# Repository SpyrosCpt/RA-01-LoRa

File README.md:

# RA-01-LoRa Dev Board

## Features
- Max 15V DC input
- 5V DC USB input
- CP2102 USB interface
- STM32F030RCT6
- 0.96" 128 x 32 OLED
- RA-01 LoRA Module
- LM35 Temperature Sensor
- AT93C46 EEPROM
- 4 Way DIP Switch
- 4 Push Buttons
- STM32 programming by SWD

## Firmware Example Provided
- Press Push Button 1 to Send LoRA Packet, you can change the data to send by editing TestLoraTransmit("packet to send")
- When not transmitting LoRA radio is in Receiver mode and will display any messages receievd
- Temperature Monitoring of LM35 will be displayed on OLED

## Hardware Version 1.1

## Firmware Change Log
- Changed frequency down from 915Mhz to 433MHz
- Oled working
- LoRa working
- EEPROM working
- Temp Sensor

## Harware Change Log
- Removed USB protection IC
- Swapped TX and RX lines
- Grounded pin 16 + 17 on OLED connector
- Moved LM34 Vcc from 3.3V to 5V

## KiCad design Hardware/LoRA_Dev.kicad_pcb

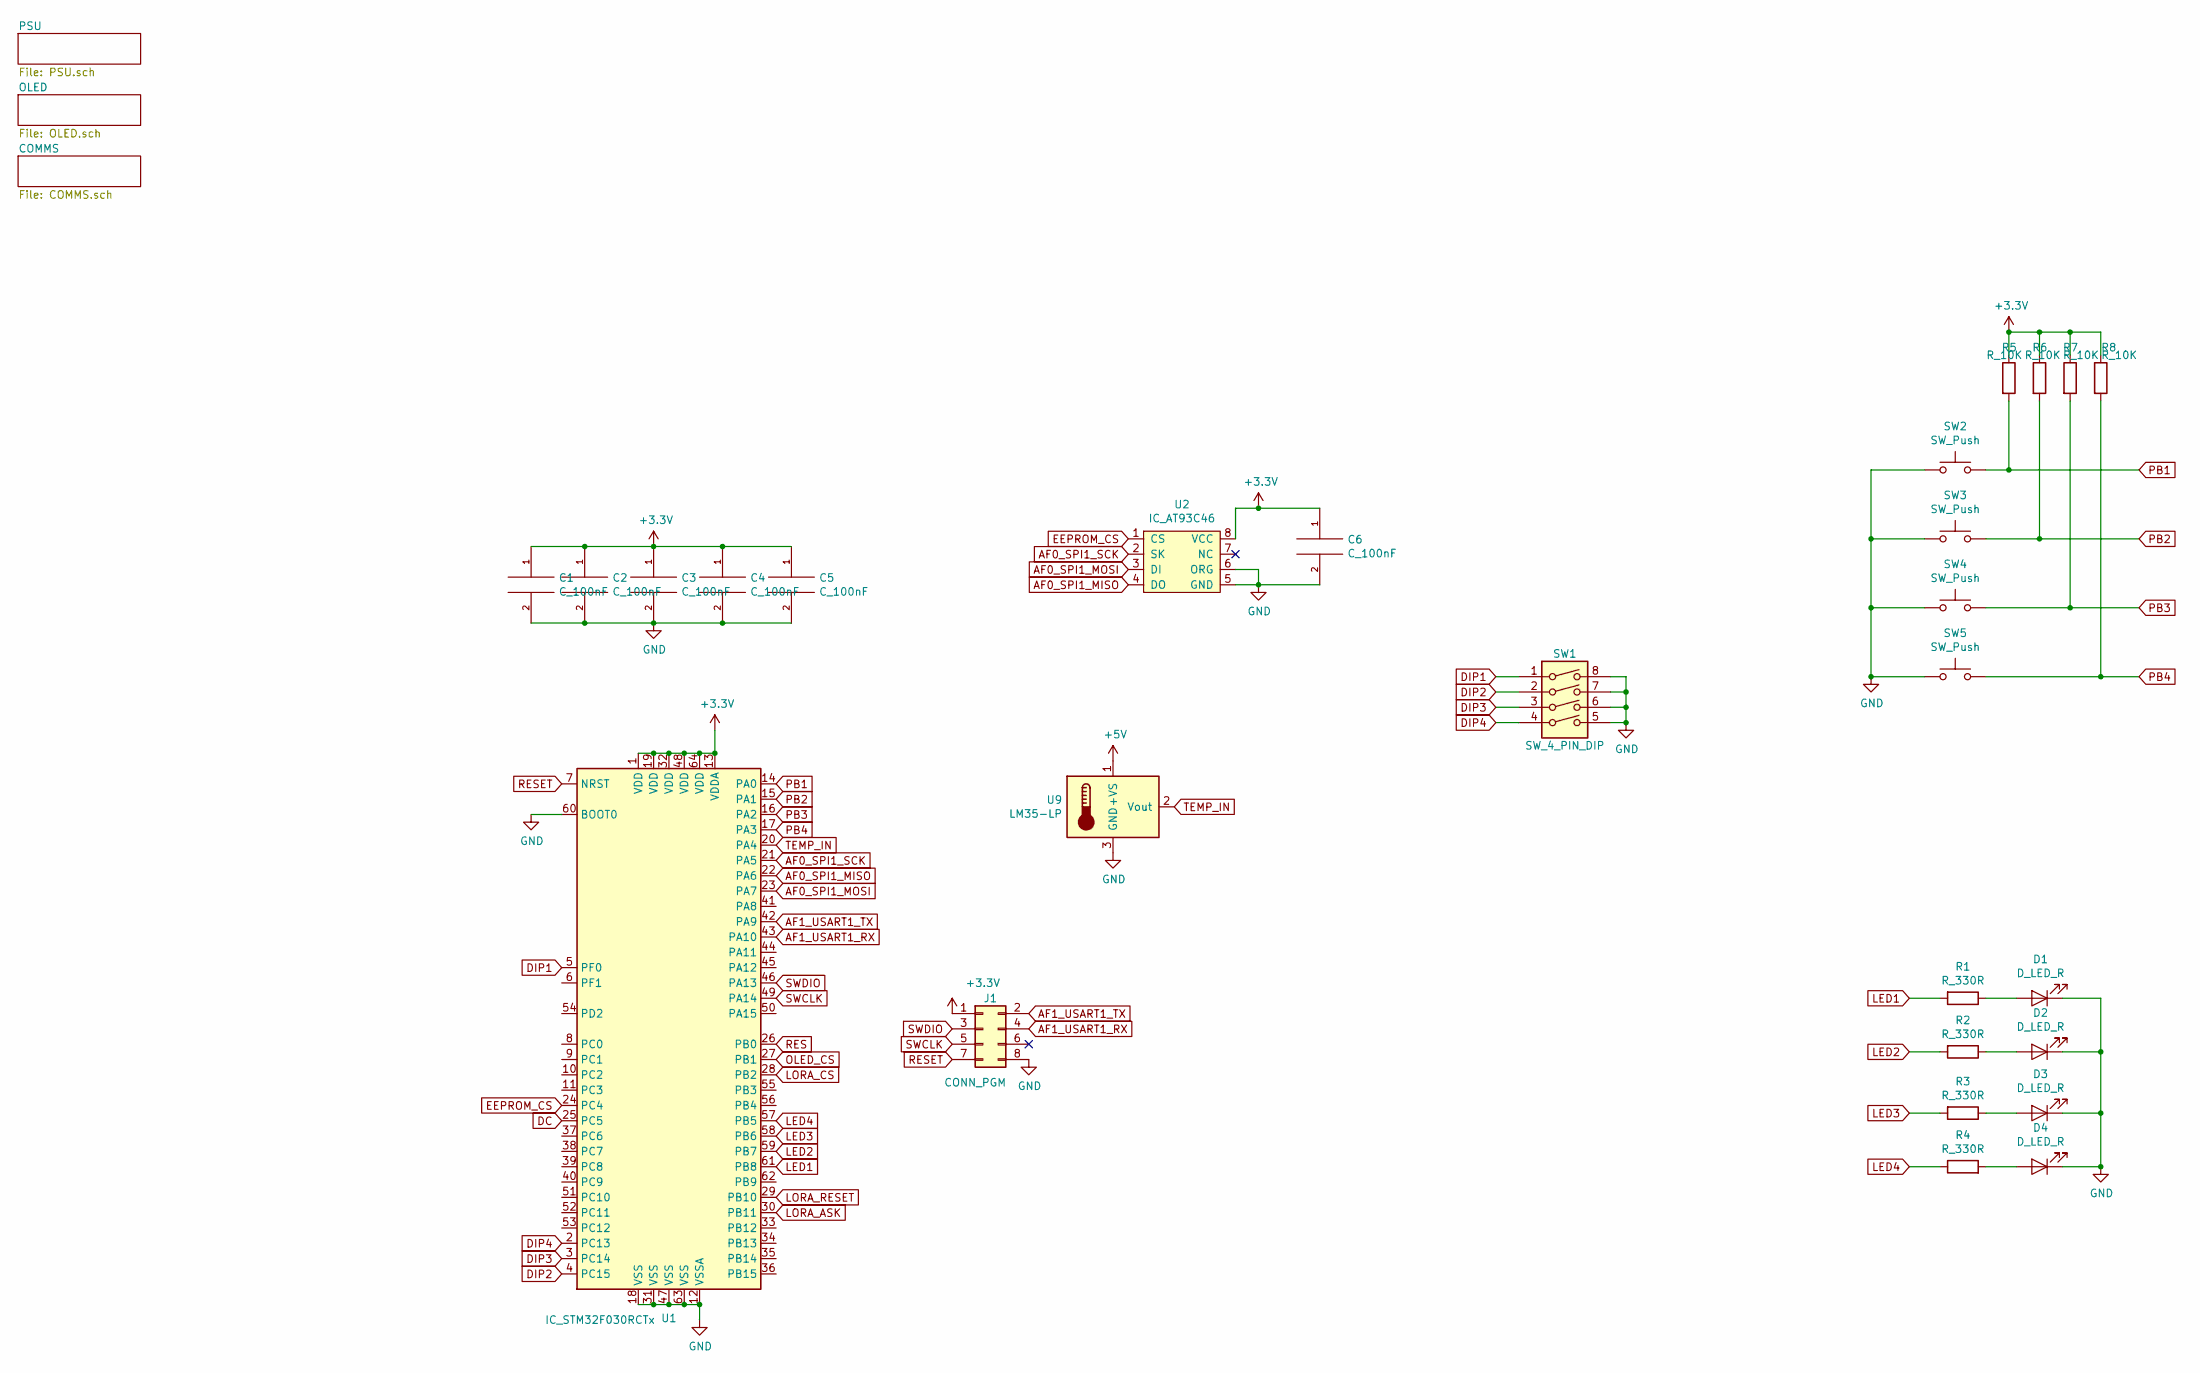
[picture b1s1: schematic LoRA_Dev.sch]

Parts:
C1, C2, C3, C4, C5, C6: C_100nF; C_0603_1608Metric_Pad1.05x0.95mm_HandSolder
D1, D2, D3, D4: D_LED_R; LED_0805_2012Metric_Pad1.15x1.40mm_HandSolder
J1: CONN_PGM; PinHeader_2x04_P2.54mm_Vertical
R1, R2, R3, R4: R_330R; R_0603_1608Metric_Pad1.05x0.95mm_HandSolder
R5, R6, R7, R8: R_10K; R_0603_1608Metric_Pad1.05x0.95mm_HandSolder
SW1: SW_4_PIN_DIP; SW_DIP_SPSTx04_Slide_9.78x12.34mm_W7.62mm_P2.54mm
SW2, SW3, SW4, SW5: SW_Push; SW_SPST_PTS645
U1: IC_STM32F030RCTx; LQFP-64_10x10mm_P0.5mm
U2: IC_AT93C46; SOIC-8_3.9x4.9mm_P1.27mm
U9: LM35-LP; TO-92

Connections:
+3V3: C1.1, C2.1, C3.1, C4.1, C5.1, C6.1, J1.1, R5.1, R6.1, R7.1, R8.1, U1.1 (VDD), U1.13 (VDDA), U1.19 (VDD), U1.32 (VDD), U1.48 (VDD), U1.64 (VDD), U2.8 (VCC); also elsewhere on the board
+5V: U9.1 (+VS); also elsewhere on the board
AF0_SPI1_MISO: U1.22 (PA6), U2.4 (DO); also elsewhere on the board
AF0_SPI1_MOSI: U1.23 (PA7), U2.3 (DI); also elsewhere on the board
AF0_SPI1_SCK: U1.21 (PA5), U2.2 (SK); also elsewhere on the board
AF1_USART1_RX: J1.4, U1.43 (PA10); also elsewhere on the board
AF1_USART1_TX: J1.2, U1.42 (PA9); also elsewhere on the board
DC: U1.25 (PC5); also elsewhere on the board
DIP1: SW1.1, U1.5 (PF0)
DIP2: SW1.2, U1.4 (PC15)
DIP3: SW1.3, U1.3 (PC14)
DIP4: SW1.4, U1.2 (PC13)
EEPROM_CS: U1.24 (PC4), U2.1 (CS)
GND: C1.2, C2.2, C3.2, C4.2, C5.2, C6.2, D1.1 (K), D2.1 (K), D3.1 (K), D4.1 (K), J1.8, SW1.5, SW1.6, SW1.7, SW1.8, SW2.1, SW3.1, SW4.1, SW5.1, U1.12 (VSSA), U1.18 (VSS), U1.31 (VSS), U1.47 (VSS), U1.60 (BOOT0), U1.63 (VSS), U2.5 (GND), U2.6 (ORG), U9.3 (GND); also elsewhere on the board
LED1: R1.2, U1.61 (PB8)
LED2: R2.2, U1.59 (PB7)
LED3: R3.2, U1.58 (PB6)
LED4: R4.1, U1.57 (PB5)
LORA_ASK: U1.30 (PB11); also elsewhere on the board
LORA_CS: U1.28 (PB2); also elsewhere on the board
LORA_RESET: U1.29 (PB10); also elsewhere on the board
unnamed: D1.2 (A), R1.1
unnamed: D2.2 (A), R2.1
unnamed: D3.2 (A), R3.1
unnamed: D4.2 (A), R4.2
OLED_CS: U1.27 (PB1); also elsewhere on the board
PB1: R5.2, SW2.2, U1.14 (PA0)
PB2: R6.2, SW3.2, U1.15 (PA1)
PB3: R7.2, SW4.2, U1.16 (PA2)
PB4: R8.2, SW5.2, U1.17 (PA3)
RES: U1.26 (PB0); also elsewhere on the board
RESET: J1.7, U1.7 (NRST)
SWCLK: J1.5, U1.49 (PA14)
SWDIO: J1.3, U1.46 (PA13)
TEMP_IN: U1.20 (PA4), U9.2 (Vout)

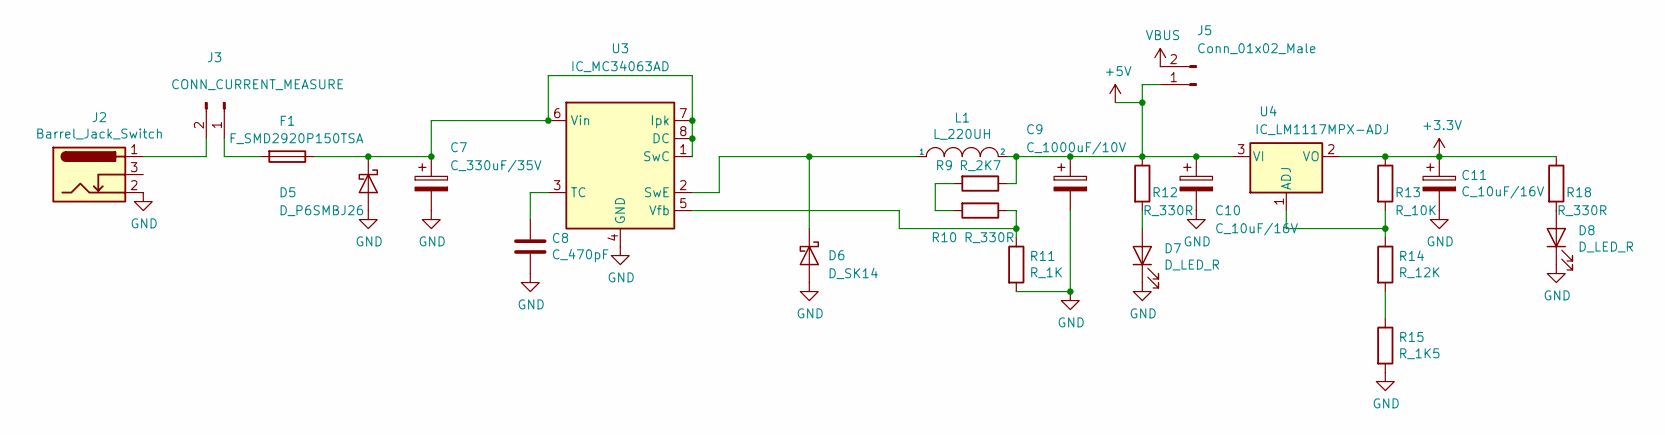
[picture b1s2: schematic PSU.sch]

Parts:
C7: C_330uF/35V; CP_Radial_D10.0mm_P5.00mm
C8: C_470pF; C_0603_1608Metric_Pad1.05x0.95mm_HandSolder
C9: C_1000uF/10V; CP_Radial_D10.0mm_P5.00mm
C10, C11: C_10uF/16V; CP_EIA-6032-28_Kemet-C_Pad2.25x2.35mm_HandSolder
D5: D_P6SMBJ26; D_SMB
D6: D_SK14; D_SMB
D7, D8: D_LED_R; LED_0805_2012Metric_Pad1.15x1.40mm_HandSolder
F1: F_SMD2920P150TSA; Fuse_2920_7451Metric_Pad2.10x5.45mm_HandSolder
J2: Barrel_Jack_Switch; BarrelJack_Horizontal
J3: CONN_CURRENT_MEASURE; PinHeader_2x01_P2.54mm_Vertical
J5: Conn_01x02_Male; PinHeader_1x02_P2.54mm_Vertical
L1: L_220UH; L_12x12mm_H8mm
R9: R_2K7; R_0603_1608Metric_Pad1.05x0.95mm_HandSolder
R10, R12, R18: R_330R; R_0603_1608Metric_Pad1.05x0.95mm_HandSolder
R11: R_1K; R_0603_1608Metric_Pad1.05x0.95mm_HandSolder
R13: R_10K; R_0603_1608Metric_Pad1.05x0.95mm_HandSolder
R14: R_12K; R_0603_1608Metric_Pad1.05x0.95mm_HandSolder
R15: R_1K5; R_0603_1608Metric_Pad1.05x0.95mm_HandSolder
U3: IC_MC34063AD; SOIC-8_3.9x4.9mm_P1.27mm
U4: IC_LM1117MPX-ADJ; SOT-223-3_TabPin2

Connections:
+3V3: C11.1, R13.1, R18.1, U4.2 (VO); also elsewhere on the board
+5V: C9.1, C10.1, J5.1, L1.2, R9.1, R12.1, U4.3 (VI); also elsewhere on the board
GND: C7.2, C8.2, C9.2, C10.2, C11.2, D5.2 (A), D6.2 (A), D7.1 (K), D8.1 (K), J2.2, R11.2, R15.2, U3.4 (GND); also elsewhere on the board
unnamed: C7.1, D5.1 (K), F1.1, U3.1 (SwC), U3.6 (Vin), U3.7 (Ipk), U3.8 (DC)
unnamed: C8.1, U3.3 (TC)
unnamed: D6.1 (K), L1.1, U3.2 (SwE)
unnamed: D7.2 (A), R12.2
unnamed: D8.2 (A), R18.2
unnamed: F1.2, J3.1
unnamed: J2.1, J3.2
unnamed: R10.1, R11.1, U3.5 (Vfb)
unnamed: R9.2, R10.2
unnamed: R13.2, R14.1, U4.1 (ADJ)
unnamed: R14.2, R15.1
VBUS: J5.2; also elsewhere on the board

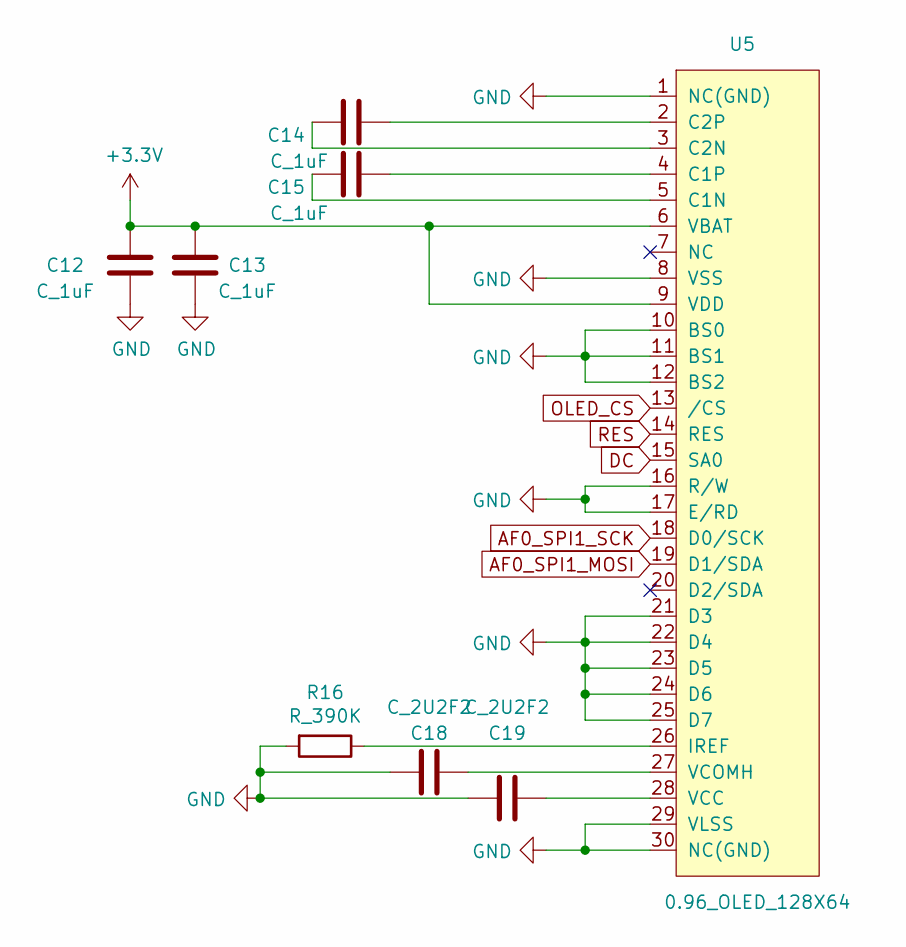
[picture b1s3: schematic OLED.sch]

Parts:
C12, C13, C14, C15: C_1uF; C_0805_2012Metric_Pad1.15x1.40mm_HandSolder
C18, C19: C_2U2F2; C_0805_2012Metric_Pad1.15x1.40mm_HandSolder
R16: R_390K; R_0603_1608Metric_Pad1.05x0.95mm_HandSolder
U5: 0.96_OLED_128X64; 0.96_OLED

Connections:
+3V3: C12.2, C13.2, U5.6 (VBAT), U5.9 (VDD); also elsewhere on the board
AF0_SPI1_MOSI: U5.19 (D1/SDA); also elsewhere on the board
AF0_SPI1_SCK: U5.18 (D0/SCK); also elsewhere on the board
DC: U5.15 (SA0); also elsewhere on the board
GND: C12.1, C13.1, C18.1, C19.1, R16.2, U5.1 (NC(GND)), U5.8 (VSS), U5.10 (BS0), U5.11 (BS1), U5.12 (BS2), U5.16 (R/W), U5.17 (E/RD), U5.21 (D3), U5.22 (D4), U5.23 (D5), U5.24 (D6), U5.25 (D7), U5.29 (VLSS), U5.30 (NC(GND)); also elsewhere on the board
unnamed: C14.1, U5.2 (C2P)
unnamed: C14.2, U5.3 (C2N)
unnamed: C15.1, U5.4 (C1P)
unnamed: C15.2, U5.5 (C1N)
unnamed: C18.2, U5.27 (VCOMH)
unnamed: C19.2, U5.28 (VCC)
unnamed: R16.1, U5.26 (IREF)
OLED_CS: U5.13 (/CS); also elsewhere on the board
RES: U5.14 (RES); also elsewhere on the board

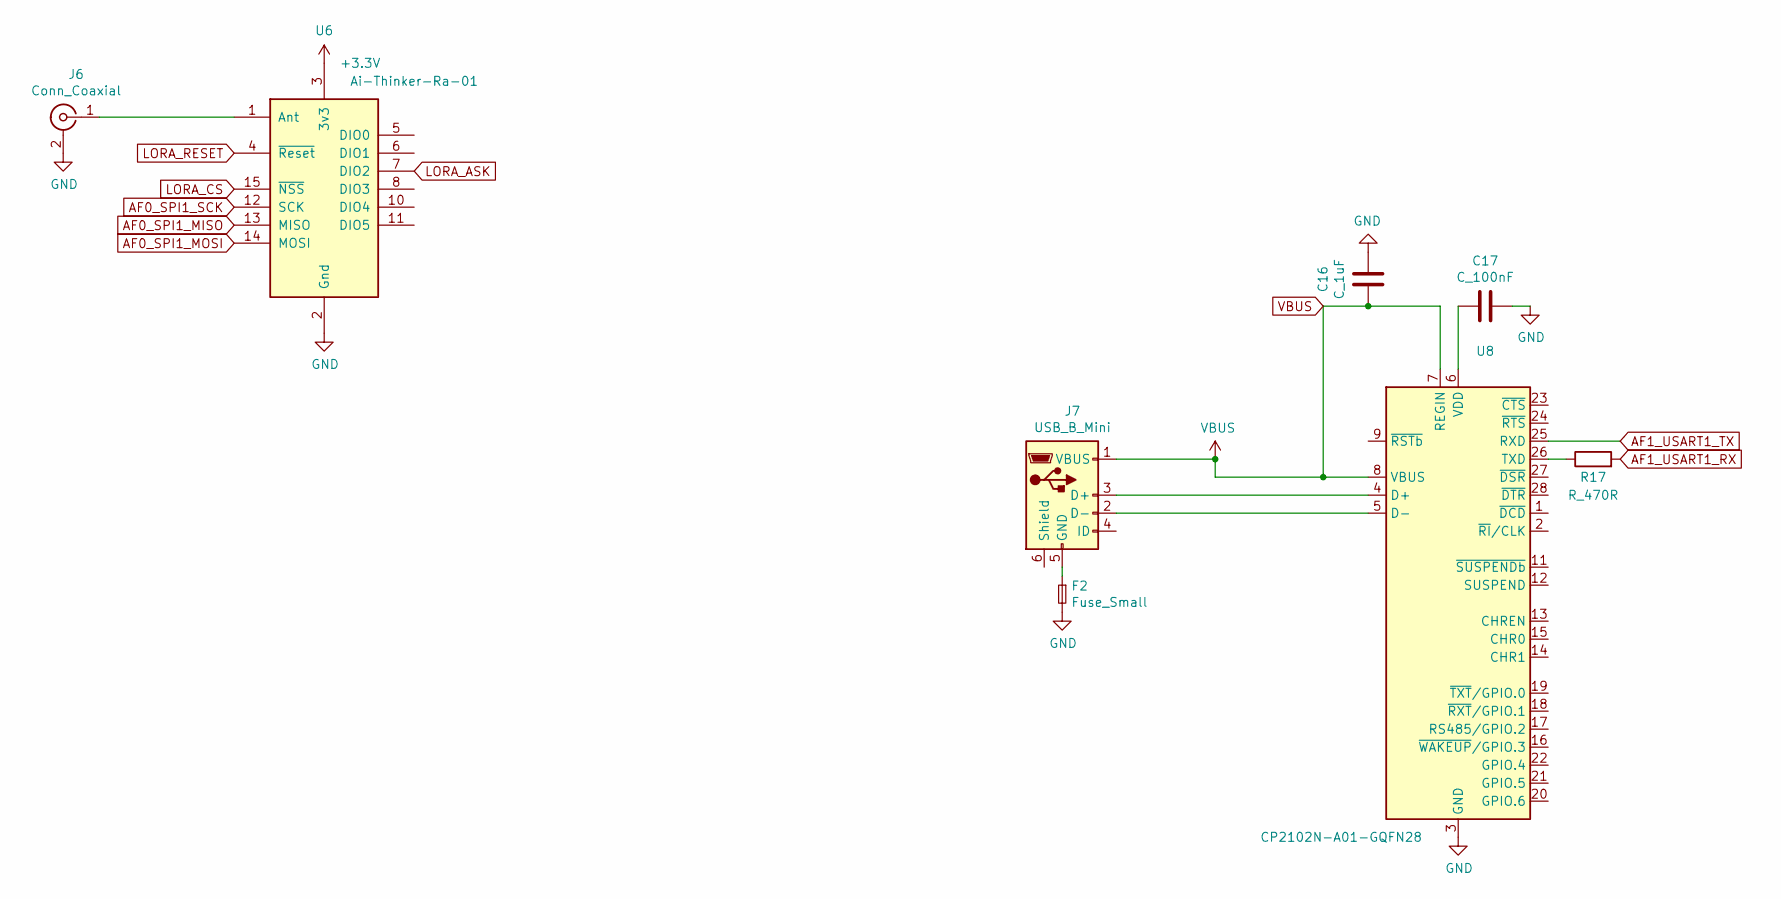
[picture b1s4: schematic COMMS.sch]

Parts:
C16: C_1uF; C_0805_2012Metric_Pad1.15x1.40mm_HandSolder
C17: C_100nF; C_0603_1608Metric_Pad1.05x0.95mm_HandSolder
F2: Fuse_Small; C_0805_2012Metric
J6: Conn_Coaxial; SMA_Amphenol_132134_Vertical
J7: USB_B_Mini; USB_Mini-B_Lumberg_2486_01_Horizontal
R17: R_470R; R_0603_1608Metric_Pad1.05x0.95mm_HandSolder
U6: Ai-Thinker-Ra-01; Ai-Thinker-Ra-01-LoRa
U8: CP2102N-A01-GQFN28; QFN-28-1EP_5x5mm_P0.5mm_EP3.35x3.35mm

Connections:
+3V3: U6.3 (3v3); also elsewhere on the board
AF0_SPI1_MISO: U6.13 (MISO); also elsewhere on the board
AF0_SPI1_MOSI: U6.14 (MOSI); also elsewhere on the board
AF0_SPI1_SCK: U6.12 (SCK); also elsewhere on the board
AF1_USART1_RX: R17.2; also elsewhere on the board
AF1_USART1_TX: U8.25 (RXD); also elsewhere on the board
GND: C16.1, C17.1, F2.2, J6.2 (Ext), U6.2 (Gnd), U6.9 (Gnd), U6.16 (Gnd), U8.3 (GND), U8.29 (GND); also elsewhere on the board
LORA_ASK: U6.7 (DIO2); also elsewhere on the board
LORA_CS: U6.15 (~NSS); also elsewhere on the board
LORA_RESET: U6.4 (~Reset); also elsewhere on the board
unnamed: C17.2, U8.6 (VDD)
unnamed: F2.1, J7.5 (GND)
unnamed: J6.1 (In), U6.1 (Ant)
unnamed: J7.2 (D-), U8.5 (D-)
unnamed: J7.3 (D+), U8.4 (D+)
unnamed: R17.1, U8.26 (TXD)
VBUS: C16.2, J7.1 (VBUS), U8.7 (REGIN), U8.8 (VBUS); also elsewhere on the board

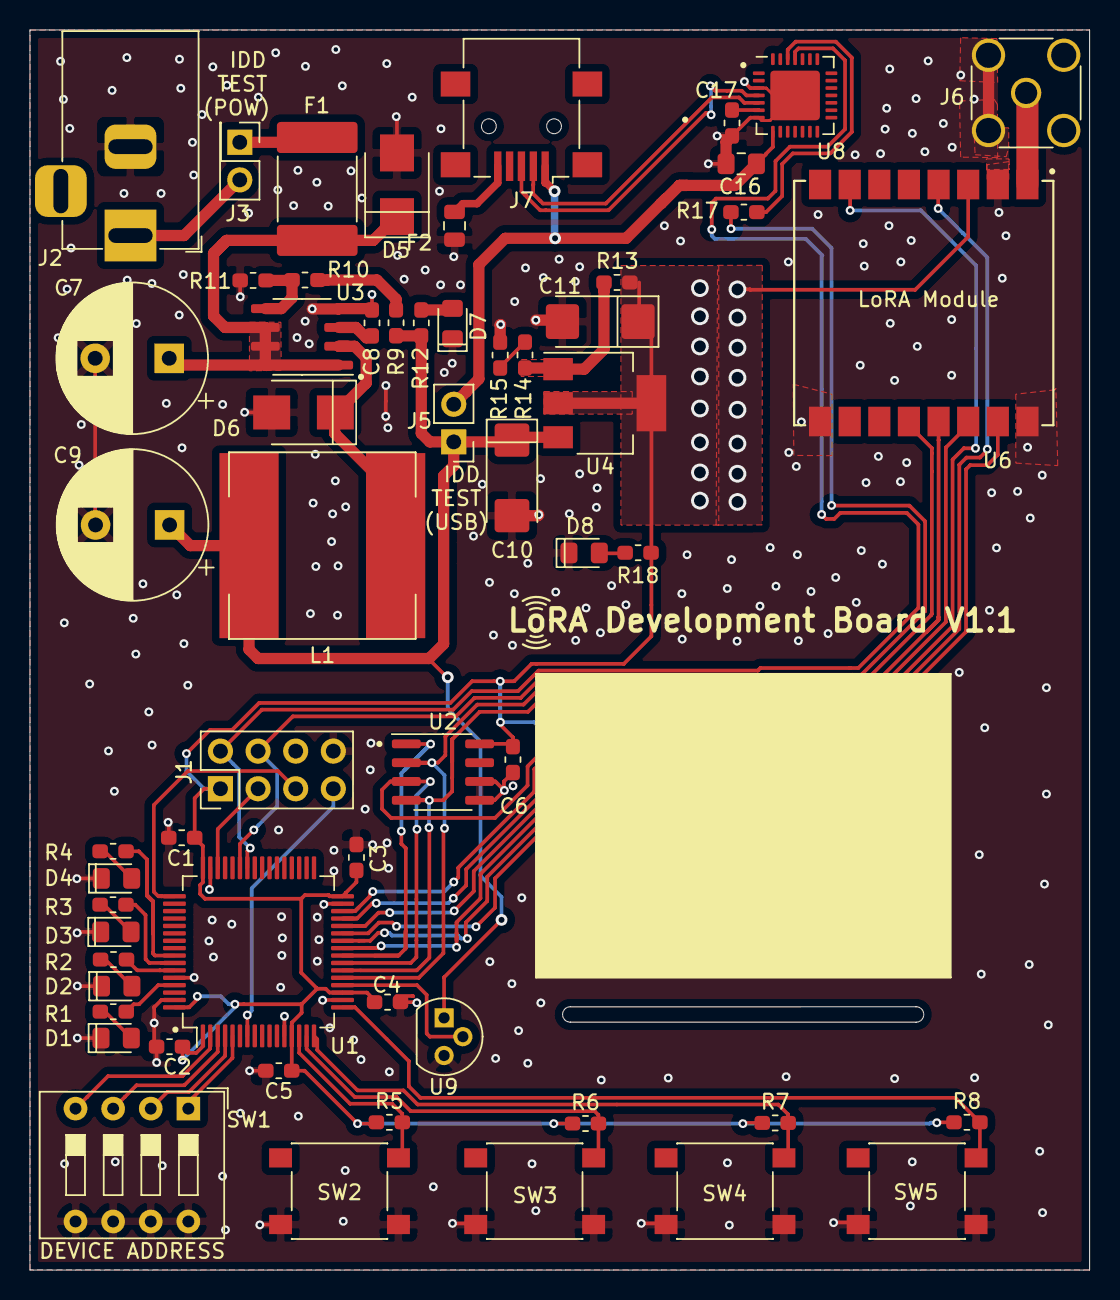
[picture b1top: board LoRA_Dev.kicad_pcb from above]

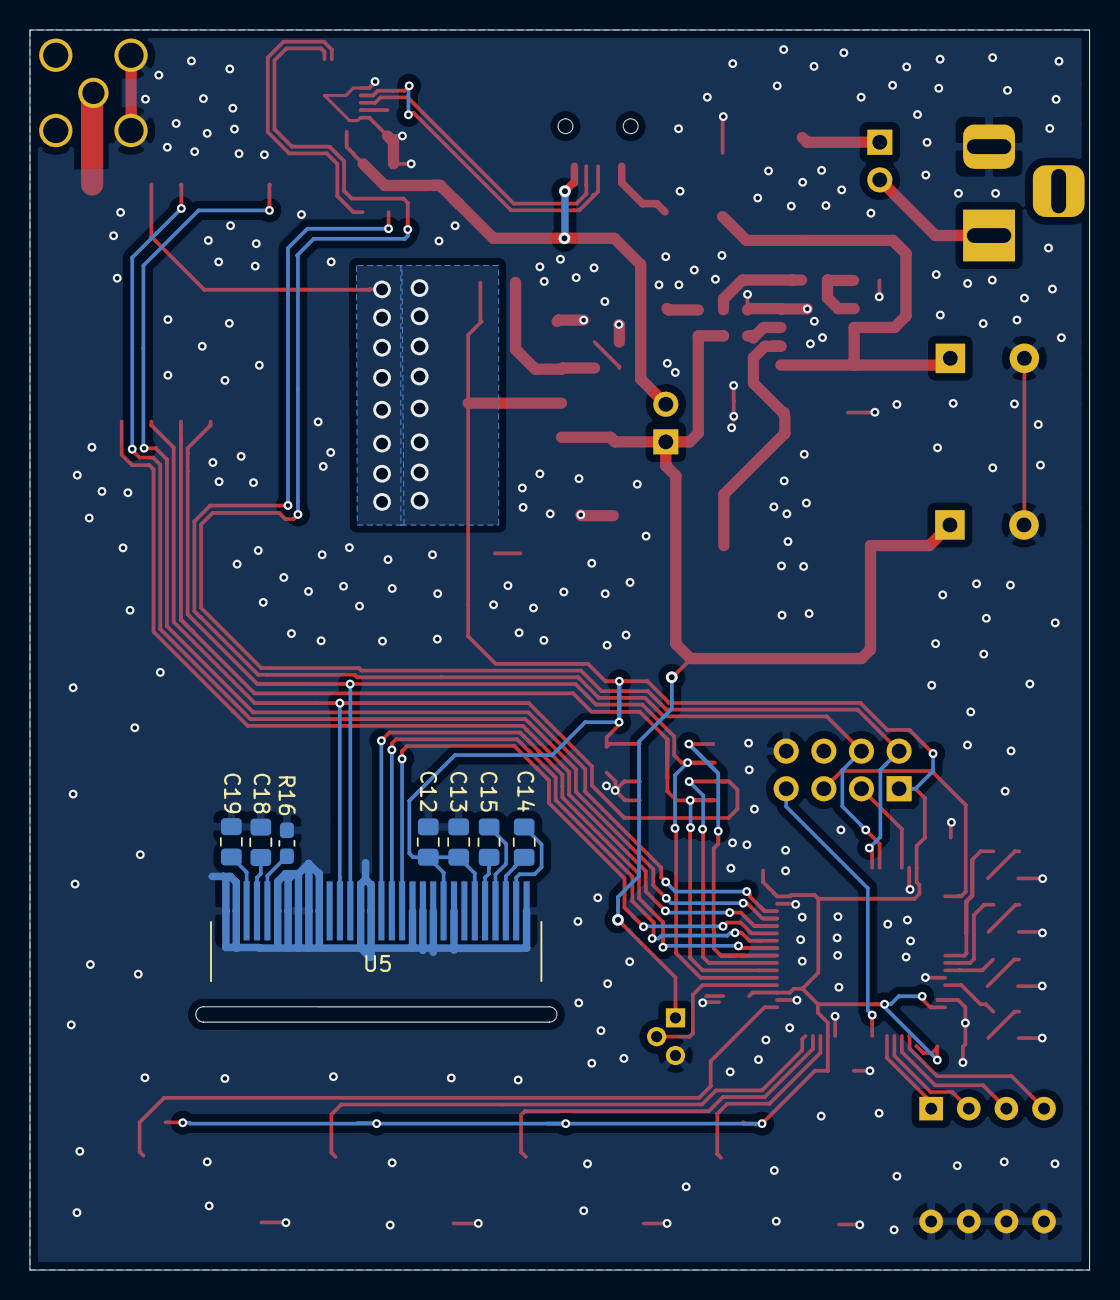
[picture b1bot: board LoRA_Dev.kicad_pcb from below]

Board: 2 copper layers, 71.5 x 83.7 mm, 67 parts (8 on the bottom side), 60 nets.

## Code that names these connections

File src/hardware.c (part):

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	Set_Pin(GPIOC,  15, INPUT, PushPull, HiSpeed, PullUp, NONE);
	Set_Pin(GPIOF,  0, INPUT, PushPull, HiSpeed, PullUp, NONE);
	
	Set_Pin(GPIOC,  4, OUTPUT, PushPull, HiSpeed, NoPull, RESET); //EEPROM_CS
	
	Set_Pin(GPIOA,  5, OUTPUT, PushPull, HiSpeed, NoPull, RESET); //CLK
	Set_Pin(GPIOA,  6, INPUT, PushPull, HiSpeed, NoPull, NONE);   //MISO
	Set_Pin(GPIOA,  7, OUTPUT, PushPull, HiSpeed, NoPull, RESET); //MOSI*/
	
	Set_Pin(GPIOB,  1, OUTPUT, PushPull, HiSpeed, NoPull, SET); //OLED_CS
	Set_Pin(GPIOC,  5, OUTPUT, PushPull, HiSpeed, NoPull, NONE); //OLED_DC
	Set_Pin(GPIOB,  0, OUTPUT, PushPull, HiSpeed, NoPull, SET); //OLED_RESET
	
	Set_Pin(GPIOB,  2, OUTPUT, PushPull, HiSpeed, NoPull, SET); //LORA_CS
	Set_Pin(GPIOB,  11, OUTPUT, PushPull, HiSpeed, NoPull, RESET); //LORA_CS
	Set_Pin(GPIOB,  10, OUTPUT, PushPull, HiSpeed, NoPull, SET); //LORA_RESET
}

/**
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	// Enable GPIOA clock
	RCC->AHBENR |= RCC_AHBENR_GPIOAEN;

	// Configure PA9 and PA10 as Alternate function
	GPIOA->MODER &= ~(GPIO_MODER_MODER9_Msk | GPIO_MODER_MODER10_Msk);
	GPIOA->MODER |= (0x02 <<GPIO_MODER_MODER9_Pos) | (0x02 <<GPIO_MODER_MODER10_Pos);

	// Set PA9 and PA10 to AF1 (USART1)
	GPIOA->AFR[1] &= ~(0x00000FF0);
	GPIOA->AFR[1] |=  (0x00000110);

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
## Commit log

2020-05-28 changed from 915 to 433Mhz
2020-05-28 Added change log
2020-05-28 cleaned up code
2020-05-28 changed
2020-05-29 updated coms.io
2020-05-29 added internal Vdd measurement for adc calibration
2020-05-30 Fixed USB, Temp sensor and OLED
2020-06-03 working on oled code
2020-06-07 font support added, bugs fixed
2020-06-07 bug fixes
2020-06-18 Add files via upload
    added 3d image of board
2020-06-18 Update README.md
    Added hardware change log
2020-06-30 updated comments and refactered
2020-07-01 removed old code
